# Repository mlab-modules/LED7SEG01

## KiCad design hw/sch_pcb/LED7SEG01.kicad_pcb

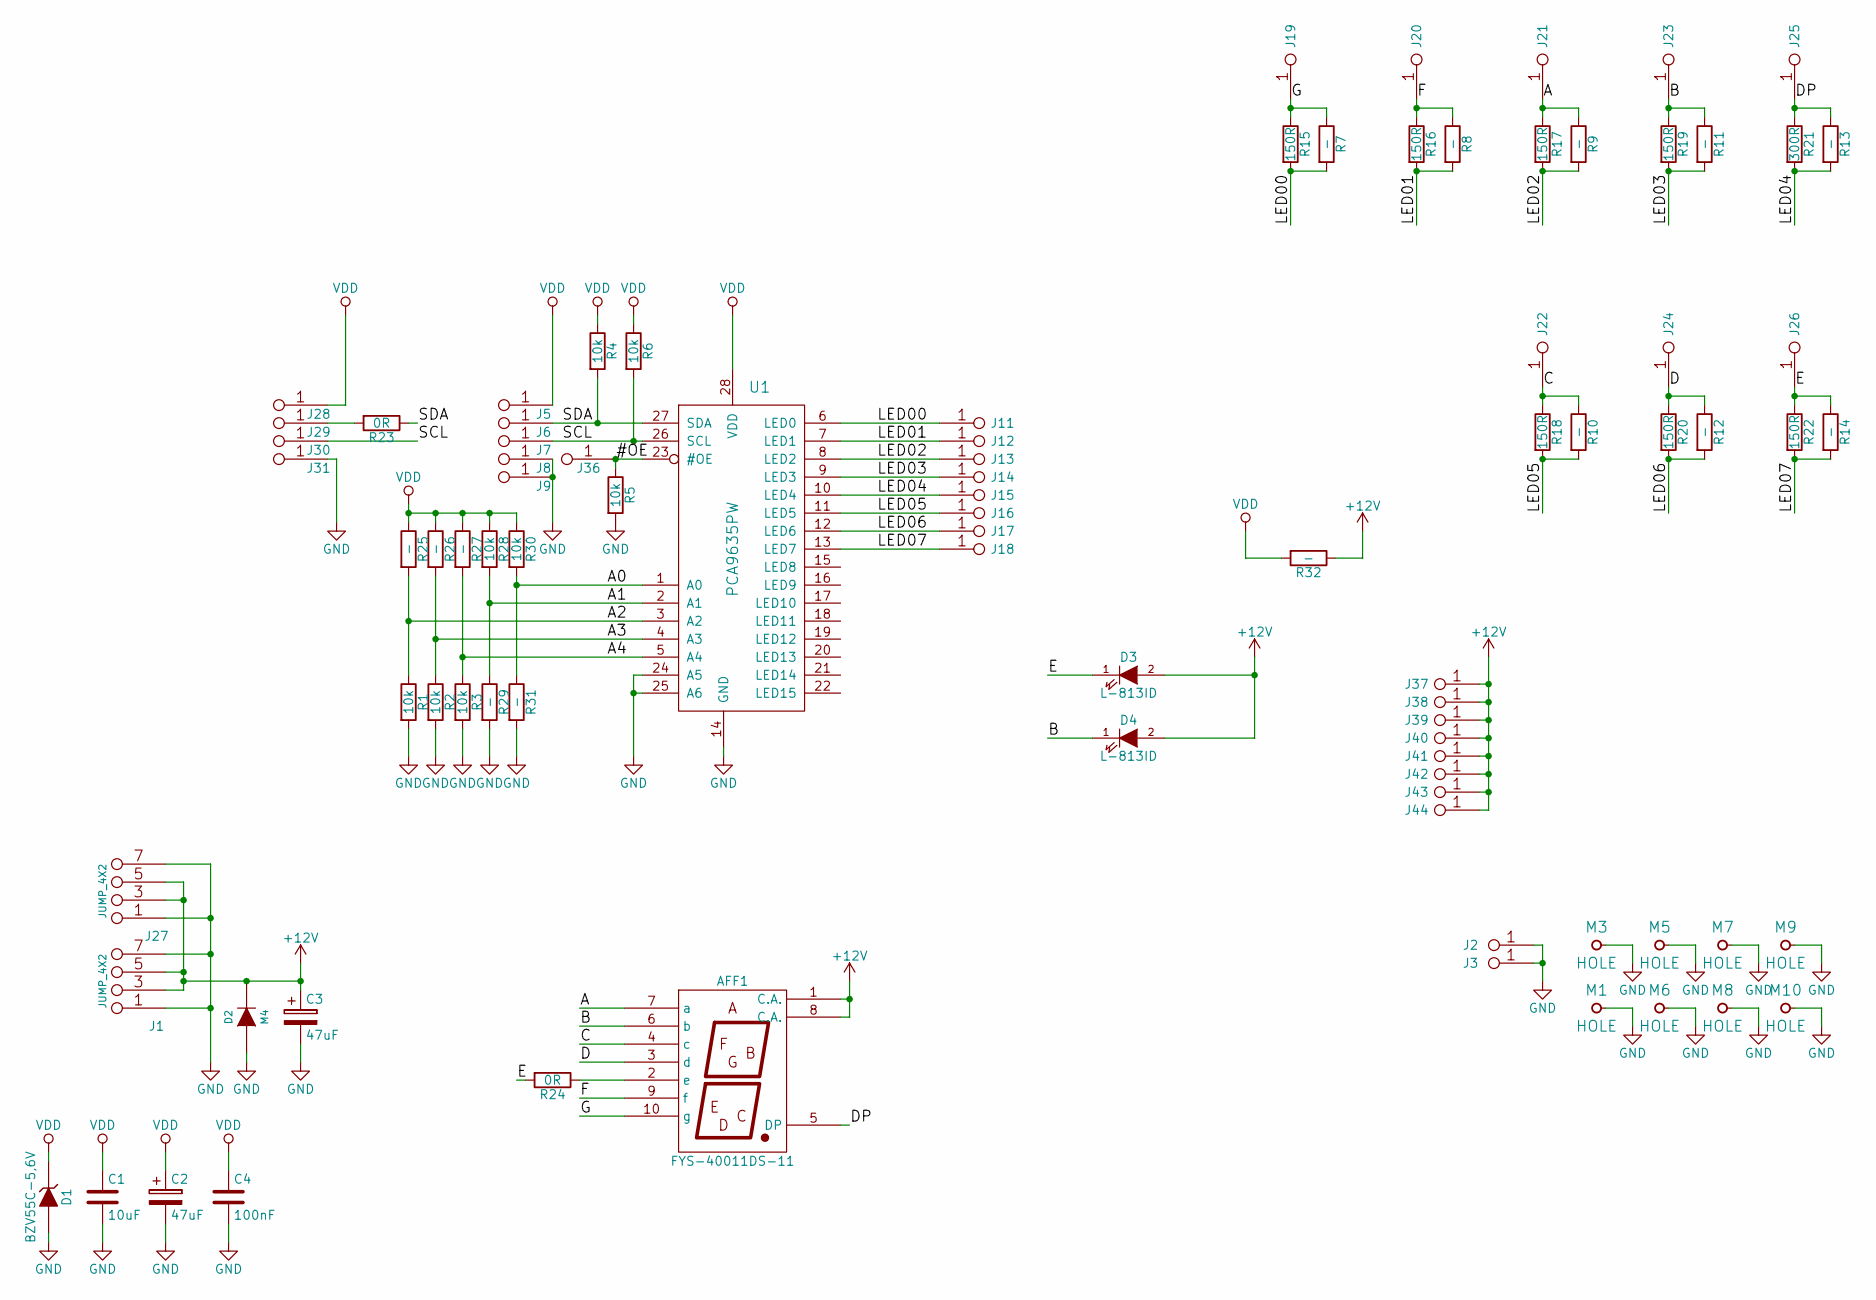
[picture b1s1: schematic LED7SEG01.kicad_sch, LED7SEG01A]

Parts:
AFF1: FYS-40011DS-11
C1: 10uF; SMD-0805
C2, C3: 47uF; TantalC_SizeC_Reflow
C4: 100nF; SMD-0805
D1: BZV55C-5,6V; MiniMELF_Standard
D2: M4; Diode-SMA_Standard
D3, D4: L-813ID; LED-10MM
J1, J27: JUMP_4X2; Straight_2x04
J2, J3: CONN1_1; 0
J5, J6, J7, J8, J9, J28, J29, J30, J31, J36: JUMP_2x1; Straight_2x01
J11, J12, J13, J14, J15, J16, J17, J18, J19, J20, J21, J22, J23, J24, J25, J26, J37, J38, J39, J40, J41, J42, J43, J44: CONN1_1; Straight_1x01
M1, M3, M5, M6, M7, M8, M9, M10: HOLE; MountingHole_3mm
R1, R2, R3, R4, R5, R6, R28, R30: 10k; SMD-0805
R7, R8, R9, R10, R11, R12, R13, R14, R25, R26, R27, R29, R31, R32: -; SMD-0805
R15, R16, R17, R18, R19, R20, R22: 150R; SMD-1206
R21: 300R; SMD-1206
R23: 0R; SMD-0805
R24: 0R; SMD-1206
U1: PCA9635PW; TSSOP28

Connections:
+12V: AFF1.1 (C.A.), AFF1.8 (C.A.), C3.1, D2.2 (K), D3.2 (A), D4.2 (A), J1.3 (4), J1.4, J1.5, J1.6 (5), J27.3 (4), J27.4, J27.5, J27.6 (5), J37.1, J38.1, J39.1, J40.1, J41.1, J42.1, J43.1, J44.1, R32.1
/#OE: J36.1, J36.2, R5.1, U1.23 (#OE)
/A: AFF1.7 (a), J21.1, R9.1, R17.1
/A0: R30.2, R31.1, U1.1 (A0)
/A1: R28.2, R29.1, U1.2 (A1)
/A2: R1.1, R25.2, U1.3 (A2)
/A3: R2.1, R26.2, U1.4 (A3)
/A4: R3.1, R27.2, U1.5 (A4)
/B: AFF1.6 (b), D4.1 (K), J23.1, R11.1, R19.1
/C: AFF1.4 (c), J22.1, R10.1, R18.1
/D: AFF1.3 (d), J24.1, R12.1, R20.1
/DP: AFF1.5 (DP), J25.1, R13.1, R21.1
/E: D3.1 (K), J26.1, R14.1, R22.1, R24.2
/F: AFF1.9 (f), J20.1, R8.1, R16.1
/G: AFF1.10 (g), J19.1, R7.1, R15.1
/LED00: J11.1, R7.2, R15.2, U1.6 (LED0)
/LED01: J12.1, R8.2, R16.2, U1.7 (LED1)
/LED02: J13.1, R9.2, R17.2, U1.8 (LED2)
/LED03: J14.1, R11.2, R19.2, U1.9 (LED3)
/LED04: J15.1, R13.2, R21.2, U1.10 (LED4)
/LED05: J16.1, R10.2, R18.2, U1.11 (LED5)
/LED06: J17.1, R12.2, R20.2, U1.12 (LED6)
/LED07: J18.1, R14.2, R22.2, U1.13 (LED7)
/SCL: J7.1, J7.2, J30.1, J30.2, R6.2, U1.26 (SCL)
/SDA: J6.1, J6.2, R4.2, R23.1, U1.27 (SDA)
GND: C1.2, C2.2, C3.2, C4.2, D1.1 (A), D2.1 (A), J1.1 (2), J1.2, J1.7 (8), J1.8, J2.1, J3.1, J8.1, J8.2, J9.1, J9.2, J27.1 (2), J27.2, J27.7 (8), J27.8, J31.1, J31.2, M1.1, M3.1, M5.1, M6.1, M7.1, M8.1, M9.1, M10.1, R1.2, R2.2, R3.2, R5.2, R29.2, R31.2, U1.14 (GND), U1.24 (A5), U1.25 (A6)
unnamed: AFF1.2 (e), R24.1
unnamed: J29.1, J29.2, R23.2
VDD: C1.1, C2.1, C4.1, D1.2 (K), J5.1, J5.2, J28.1, J28.2, R4.1, R6.1, R25.1, R26.1, R27.1, R28.1, R30.1, R32.2, U1.28 (VDD)

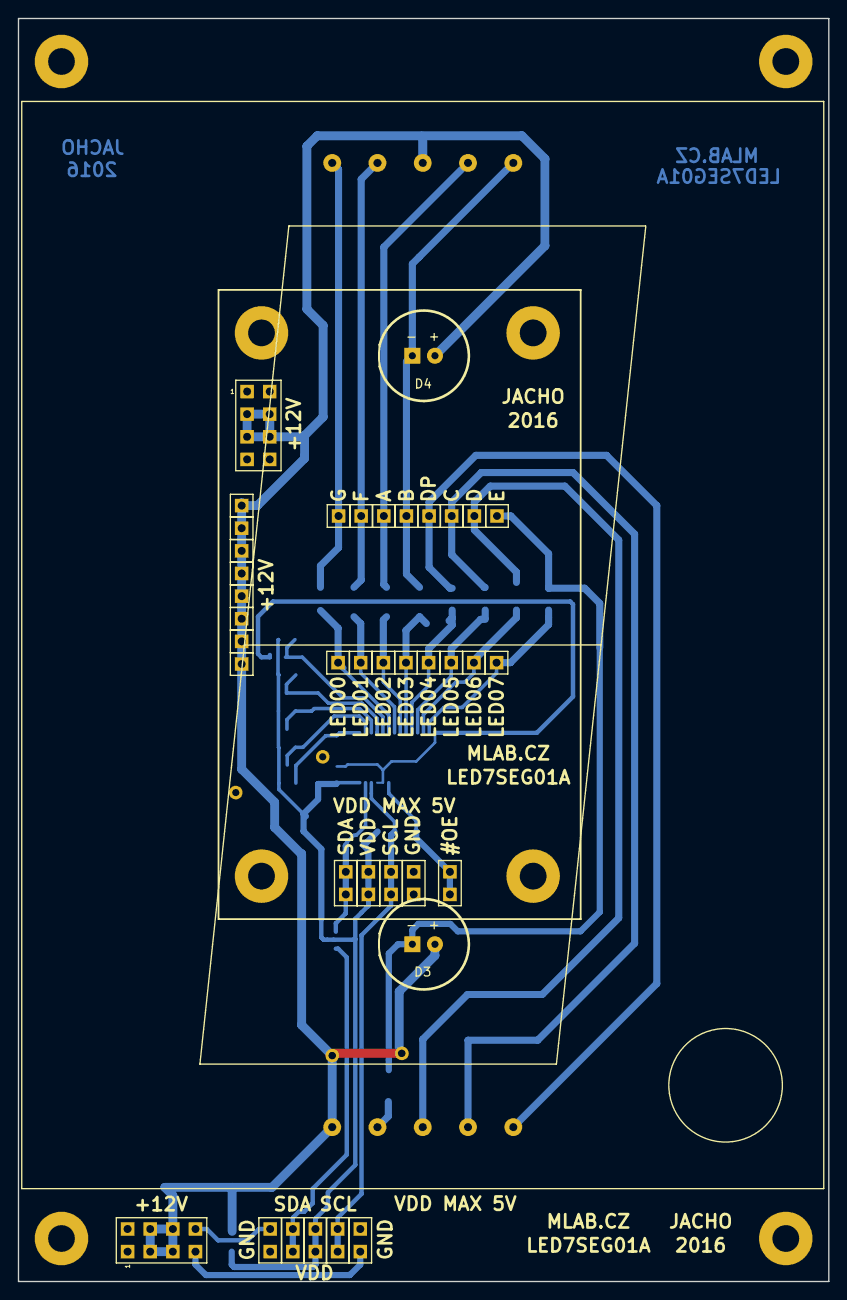
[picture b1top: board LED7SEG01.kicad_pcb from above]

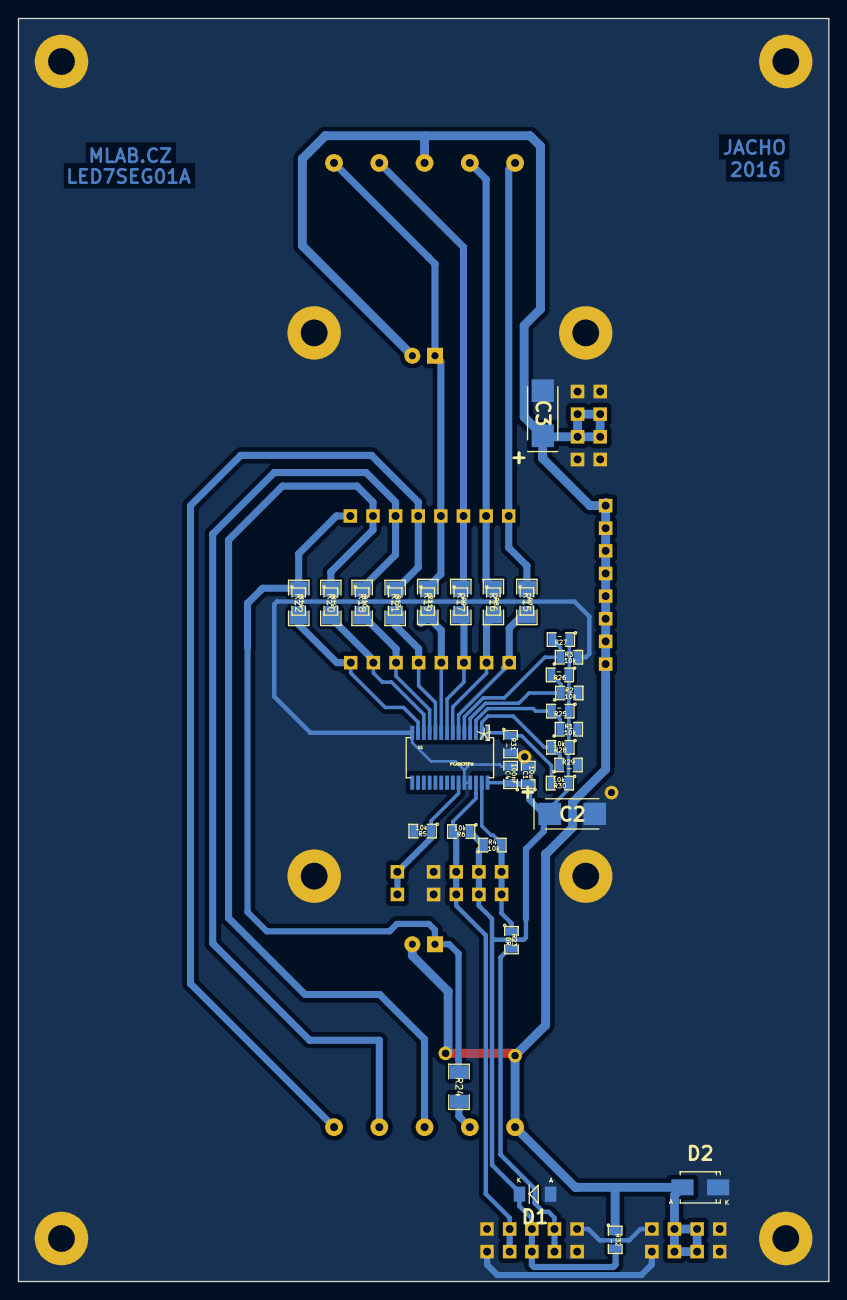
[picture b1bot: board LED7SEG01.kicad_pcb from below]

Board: 2 copper layers, 90.9 x 141.7 mm, 88 parts (39 on the bottom side), 29 nets.

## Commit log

2023-04-01 Adding force option to enable splitting in not fresh copy of Modules repository.
2023-07-04 automated commit; add github actions
2023-07-04 Update workflow files
2023-07-04 Update metadata files
2023-07-05 automated commit; rename source files to new naming convence
2023-09-16 Update status
2023-09-17 Convert project to KiCADv7
2023-09-17 Update actions products
2023-09-17 Update metadata.yaml
    Select title image.
